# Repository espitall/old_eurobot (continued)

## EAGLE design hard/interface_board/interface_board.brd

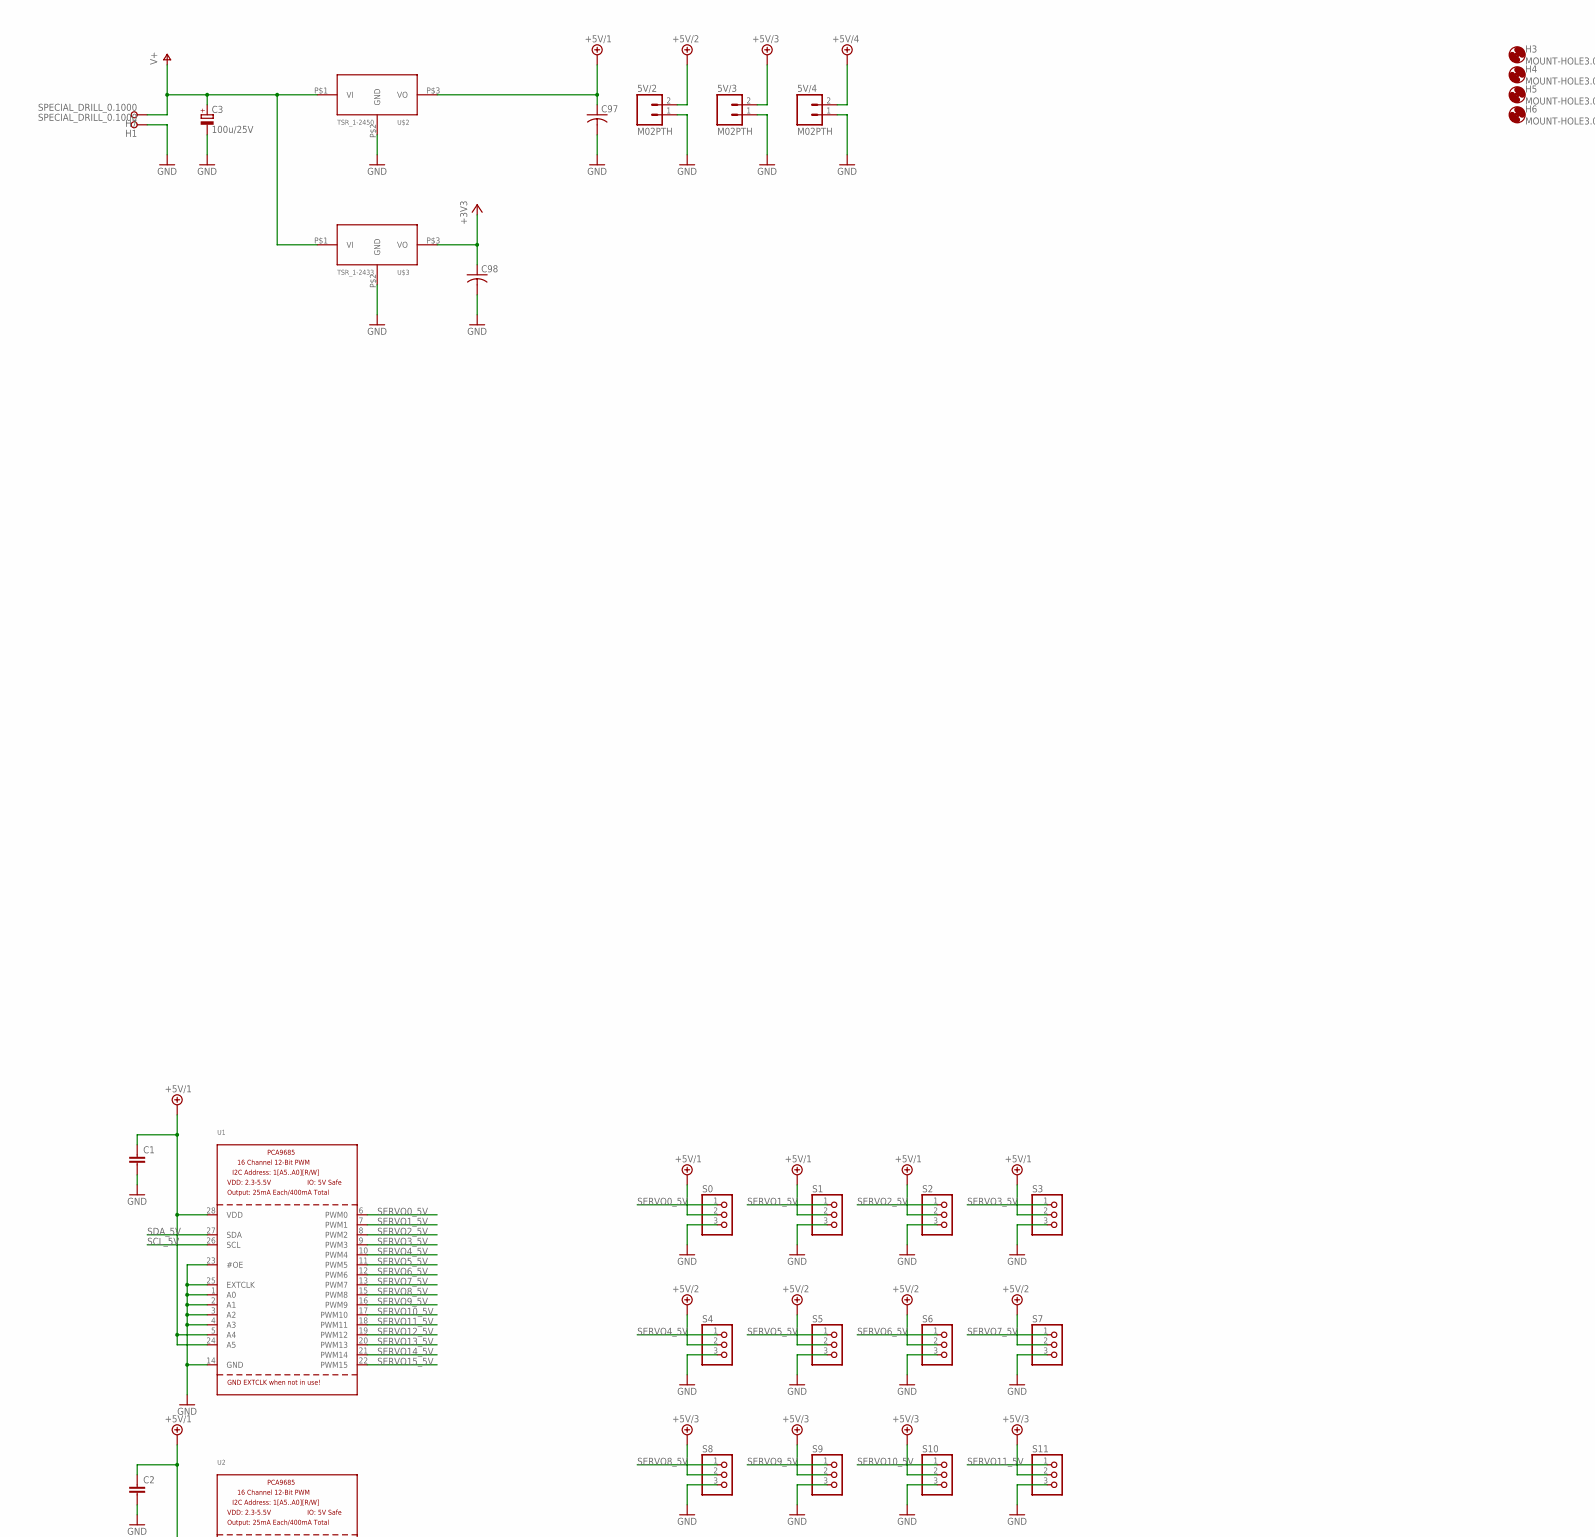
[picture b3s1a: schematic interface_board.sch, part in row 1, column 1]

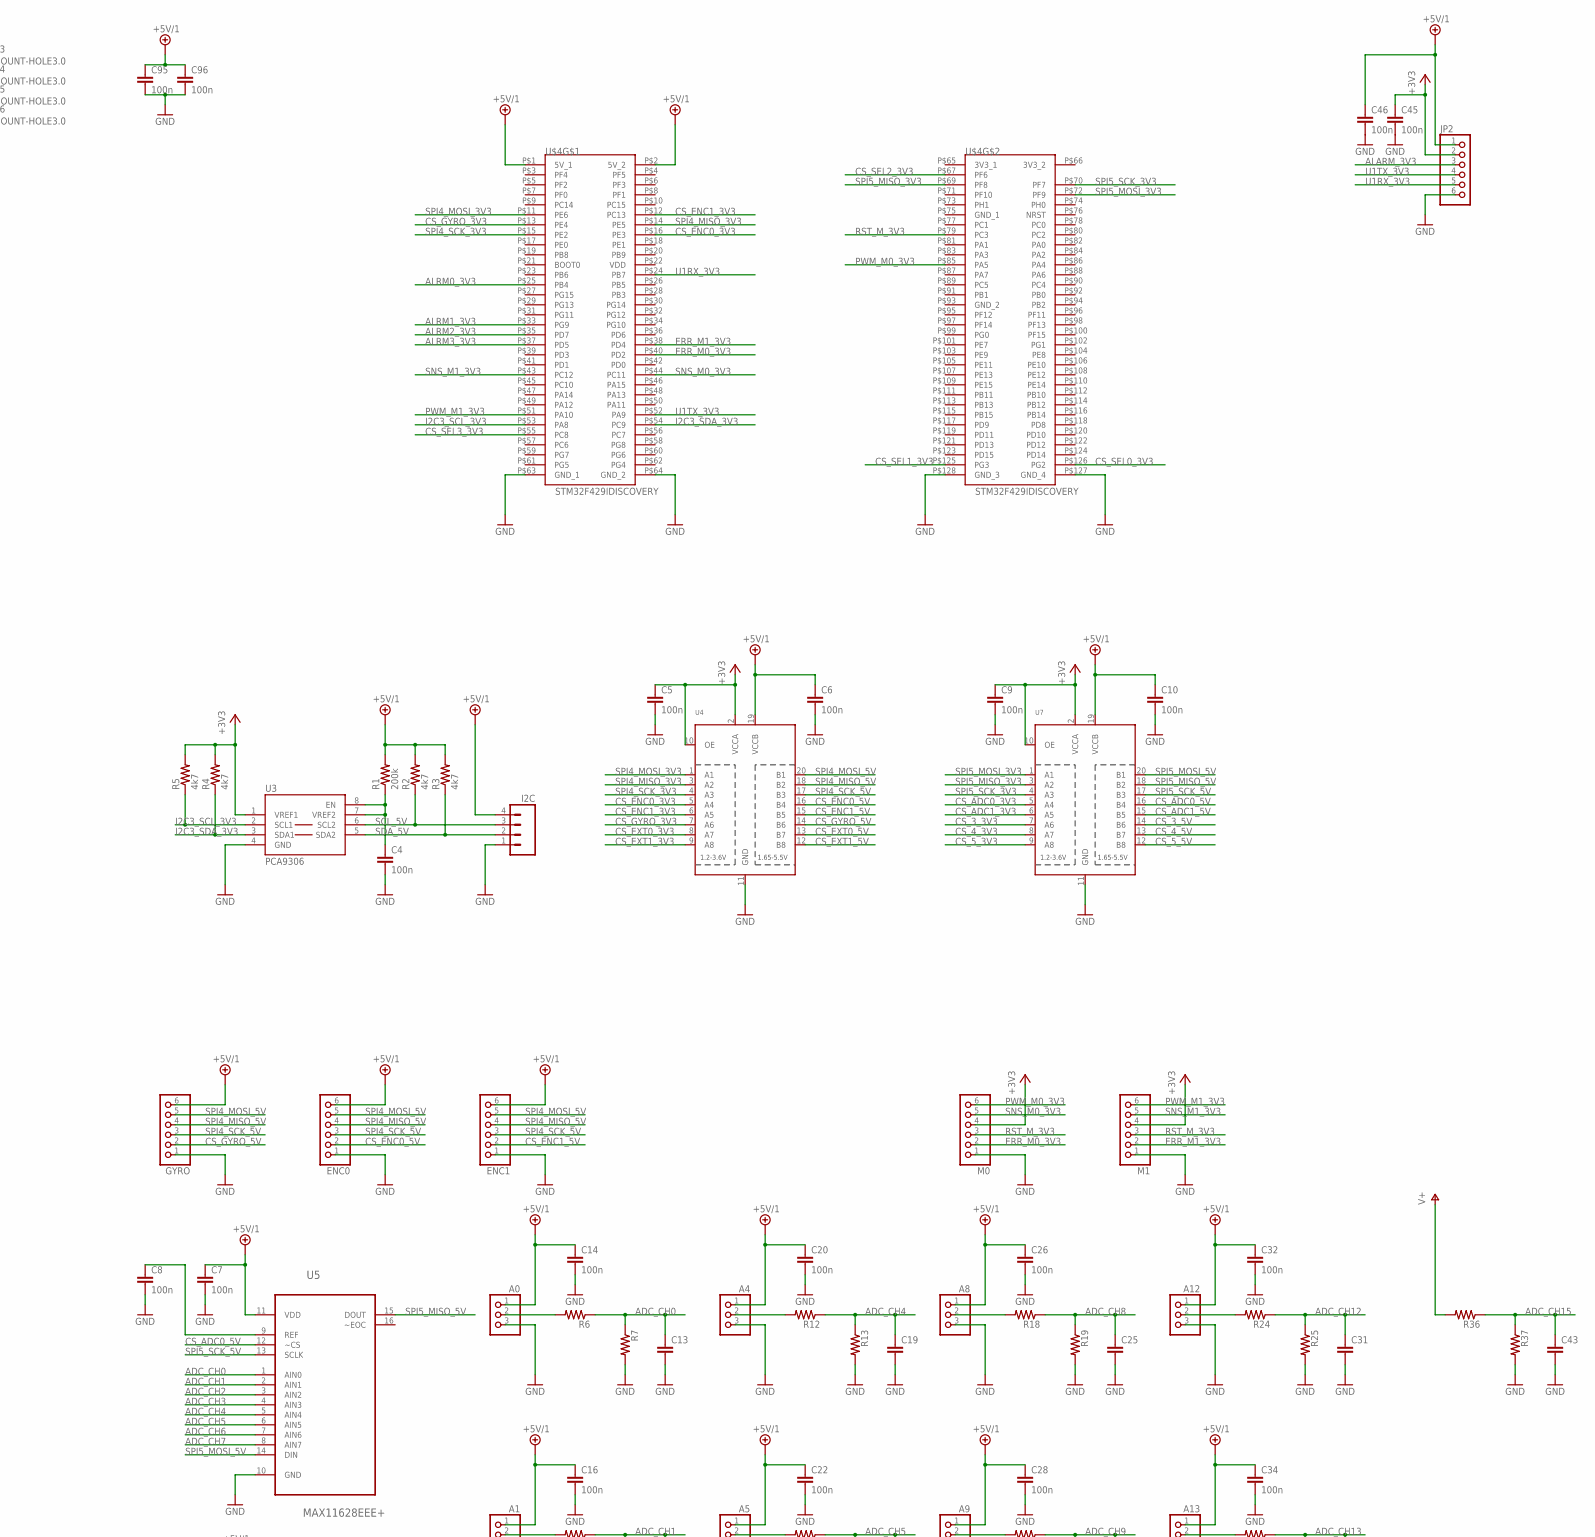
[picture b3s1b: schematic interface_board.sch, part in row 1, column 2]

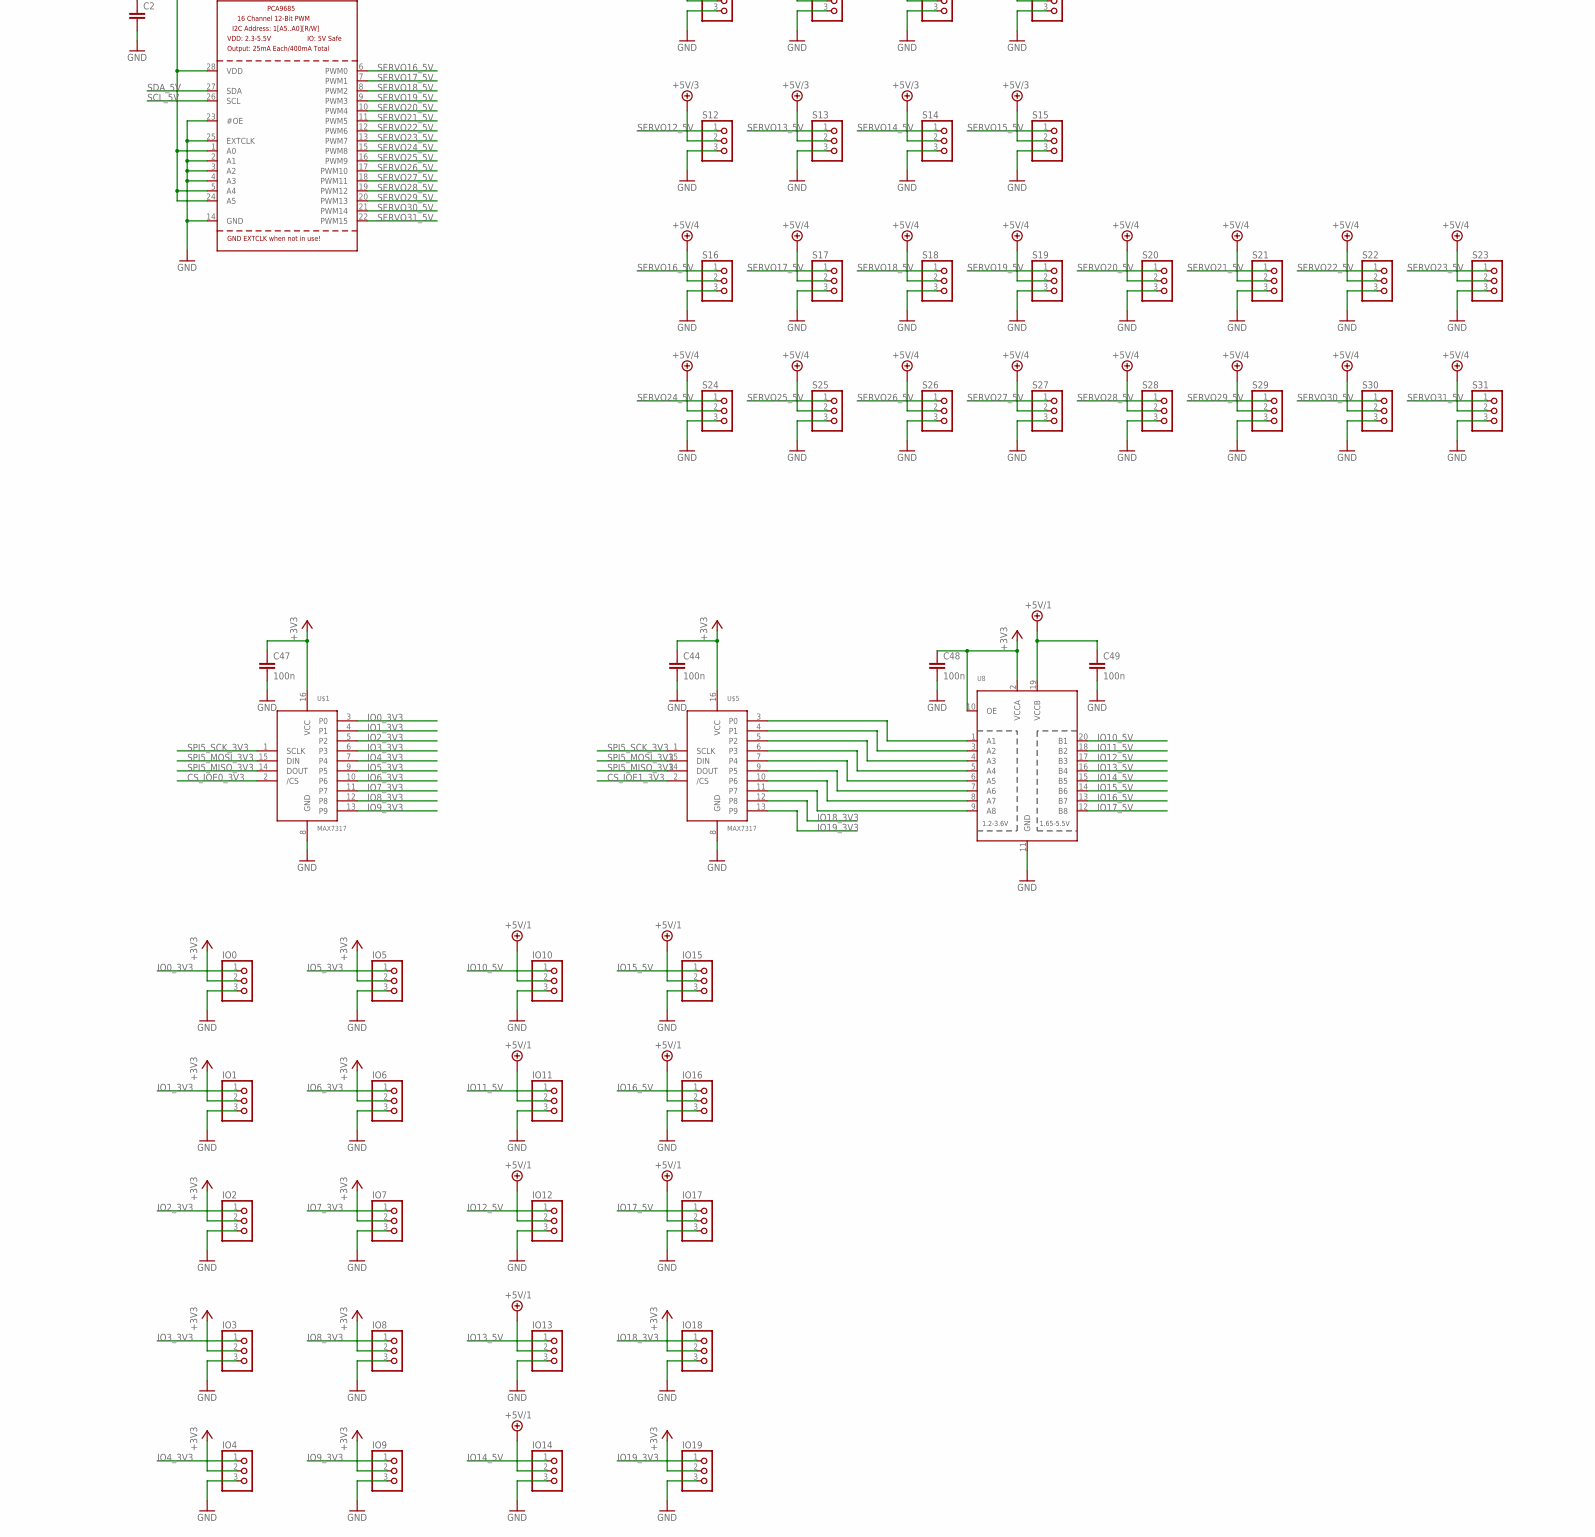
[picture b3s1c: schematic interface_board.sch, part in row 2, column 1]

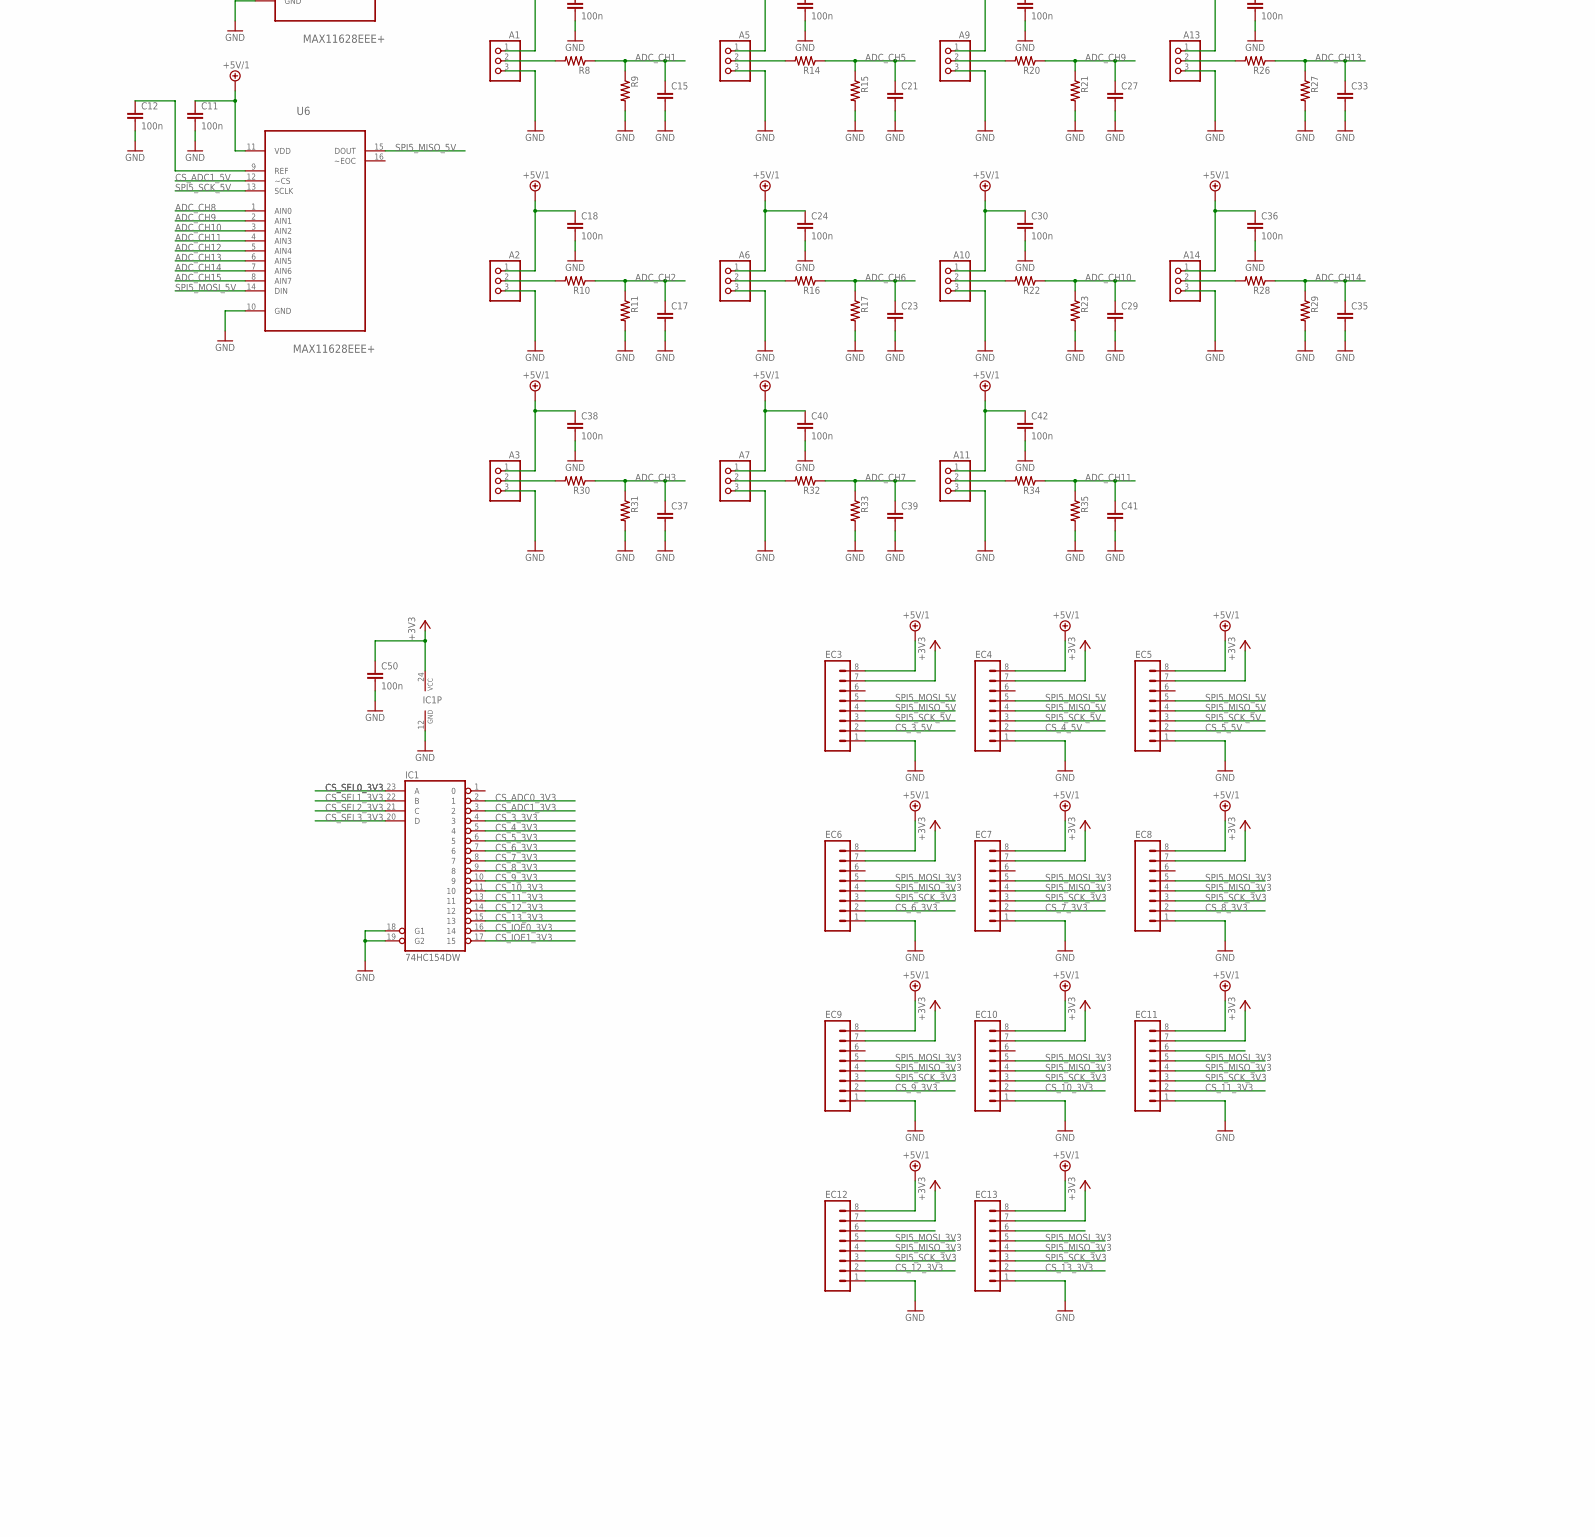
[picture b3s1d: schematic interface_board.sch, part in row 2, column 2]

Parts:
5V/2, 5V/3, 5V/4: M02PTH; 1X02
A0, A1, A2, A3, A4, A5, A6, A7, A8, A9, A10, A11, A12, A13, A14: PINHD-1X3; 1X03
C1, C2, C13, C15, C17, C19, C21, C23, C25, C27, C29, C31, C33, C35, C37, C39, C41, C43: C-EUC0603K; C0603K
C3: 100u/25V; PANASONIC_E
C4, C5, C6, C7, C8, C9, C10, C11, C12, C14, C16, C18, C20, C22, C24, C26, C28, C30, C32, C34, C36, C38, C40, C42, C44, C45, C46, C47, C48, C49, C50, C95, C96: 100n; C0603K
C97, C98: C-USC0805; C0805
EC3, EC4, EC5, EC6, EC7, EC8, EC9, EC10, EC11, EC12, EC13: M081X08; 1X08
ENC0, ENC1: PINHD-1X6; 1X06
GYRO: PINHD-1X6; 1X06
H1, H7: SPECIAL_DRILL_0.1000; PAD_0.1000
H3, H4, H5, H6: MOUNT-HOLE3.0; 3,0
I2C: M04PTH; 1X04
IC1: 74HC154DW; SO24W
IO0, IO1, IO2, IO3, IO4, IO5, IO6, IO7, IO8, IO9, IO10, IO11, IO12, IO13, IO14, IO15, IO16, IO17, IO18, IO19: PINHD-1X3; 1X03
JP2: PINHD-1X6B; 1X06-BIG
M0, M1: PINHD-1X6; 1X06
R1: 200k; R0603
R2, R3, R4, R5: 4k7; R0603
R6, R7, R8, R9, R10, R11, R12, R13, R14, R15, R16, R17, R18, R19, R20, R21, R22, R23, R24, R25, R26, R27, R28, R29, R30, R31, R32, R33, R34, R35, R36, R37: R-US_R0603; R0603
S0, S1, S2, S3, S4, S5, S6, S7, S8, S9, S10, S11, S12, S13, S14, S15, S16, S17, S18, S19, S20, S21, S22, S23, S24, S25, S26, S27, S28, S29, S30, S31: PINHD-1X3; 1X03
U1, U2: PCA9685; TSSOP28
U3: PCA9306; PSOP-8
U4, U7, U8: TXB0108PWR; TSSOP20
U5, U6: MAX11628EEE+; SOP63P602X175-16N
U$1, U$5: MAX7317; SOP63P600X175-16N
U$2: TSR_1-2450; TSR-1
U$3: TSR_1-2433; TSR-1
U$4: STM32F429IDISCOVERY

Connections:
+3V3: C5.1, C9.1, C44.1, C45.1, C47.1, C48.1, C50.1, C98.1, EC3.7, EC4.7, EC5.7, EC6.7, EC7.7, EC8.7, EC9.7, EC10.7, EC11.7, EC12.7, EC13.7, IC1.24 (VCC), IO0.2, IO1.2, IO2.2, IO3.2, IO4.2, IO5.2, IO6.2, IO7.2, IO8.2, IO9.2, IO18.2, IO19.2, JP2.2, M0.4, M1.4, R4.2, R5.2, U3.1 (VREF1), U4.2 (VCCA), U4.10 (OE), U7.2 (VCCA), U7.10 (OE), U8.2 (VCCA), U8.10 (OE), U$1.16 (VCC), U$3.P$3 (VO), U$5.16 (VCC)
+5V/1: A0.1, A1.1, A2.1, A3.1, A4.1, A5.1, A6.1, A7.1, A8.1, A9.1, A10.1, A11.1, A12.1, A13.1, A14.1, C1.1, C2.1, C6.1, C7.1, C10.1, C11.1, C14.1, C16.1, C18.1, C20.1, C22.1, C24.1, C26.1, C28.1, C30.1, C32.1, C34.1, C36.1, C38.1, C40.1, C42.1, C46.1, C49.1, C95.1, C96.1, C97.1, EC3.8, EC4.8, EC5.8, EC6.8, EC7.8, EC8.8, EC9.8, EC10.8, EC11.8, EC12.8, EC13.8, ENC0.6, ENC1.6, GYRO.6, I2C.4, IO10.2, IO11.2, IO12.2, IO13.2, IO14.2, IO15.2, IO16.2, IO17.2, JP2.1, R1.2, R2.2, R3.2, S0.2, S1.2, S2.2, S3.2, U1.5 (A4), U1.24 (A5), U1.28 (VDD), U2.1 (A0), U2.5 (A4), U2.24 (A5), U2.28 (VDD), U4.19 (VCCB), U5.11 (VDD), U6.11 (VDD), U7.19 (VCCB), U8.19 (VCCB), U$2.P$3 (VO), U$4.P$1 (5V_1), U$4.P$2 (5V_2)
+5V/2: 5V/2.2, S4.2, S5.2, S6.2, S7.2
+5V/3: 5V/3.2, S8.2, S9.2, S10.2, S11.2, S12.2, S13.2, S14.2, S15.2
+5V/4: 5V/4.2, S16.2, S17.2, S18.2, S19.2, S20.2, S21.2, S22.2, S23.2, S24.2, S25.2, S26.2, S27.2, S28.2, S29.2, S30.2, S31.2
ADC_CH0: C13.1, R6.1, R7.1, U5.1 (AIN0)
ADC_CH1: C15.1, R8.1, R9.1, U5.2 (AIN1)
ADC_CH2: C17.1, R10.1, R11.1, U5.3 (AIN2)
ADC_CH3: C37.1, R30.1, R31.1, U5.4 (AIN3)
ADC_CH4: C19.1, R12.1, R13.1, U5.5 (AIN4)
ADC_CH5: C21.1, R14.1, R15.1, U5.6 (AIN5)
ADC_CH6: C23.1, R16.1, R17.1, U5.7 (AIN6)
ADC_CH7: C39.1, R32.1, R33.1, U5.8 (AIN7)
ADC_CH8: C25.1, R18.1, R19.1, U6.1 (AIN0)
ADC_CH9: C27.1, R20.1, R21.1, U6.2 (AIN1)
ADC_CH10: C29.1, R22.1, R23.1, U6.3 (AIN2)
ADC_CH11: C41.1, R34.1, R35.1, U6.4 (AIN3)
ADC_CH12: C31.1, R24.1, R25.1, U6.5 (AIN4)
ADC_CH13: C33.1, R26.1, R27.1, U6.6 (AIN5)
ADC_CH14: C35.1, R28.1, R29.1, U6.7 (AIN6)
ADC_CH15: C43.1, R36.1, R37.1, U6.8 (AIN7)
ALARM_3V3: JP2.3
ALRM0_3V3: U$4.P$25 (PB4)
ALRM1_3V3: EC11.6, U$4.P$33 (PG9)
ALRM2_3V3: EC12.6, U$4.P$35 (PD7)
ALRM3_3V3: EC13.6, U$4.P$37 (PD5)
CS_3_3V3: IC1.4 (3), U7.7 (A6)
CS_3_5V: EC3.2, U7.14 (B6)
CS_4_3V3: IC1.5 (4), U7.8 (A7)
CS_4_5V: EC4.2, U7.13 (B7)
CS_5_3V3: IC1.6 (5), U7.9 (A8)
CS_5_5V: EC5.2, U7.12 (B8)
CS_6_3V3: EC6.2, IC1.7 (6)
CS_7_3V3: EC7.2, IC1.8 (7)
CS_8_3V3: EC8.2, IC1.9 (8)
CS_9_3V3: EC9.2, IC1.10 (9)
CS_10_3V3: EC10.2, IC1.11 (10)
CS_11_3V3: EC11.2, IC1.13 (11)
CS_12_3V3: EC12.2, IC1.14 (12)
CS_13_3V3: EC13.2, IC1.15 (13)
CS_ADC0_3V3: IC1.2 (1), U7.5 (A4)
CS_ADC0_5V: U5.12 (~CS), U7.16 (B4)
CS_ADC1_3V3: IC1.3 (2), U7.6 (A5)
CS_ADC1_5V: U6.12 (~CS), U7.15 (B5)
CS_ENC0_3V3: U4.5 (A4), U$4.P$16 (PE3)
CS_ENC0_5V: ENC0.2, U4.16 (B4)
CS_ENC1_3V3: U4.6 (A5), U$4.P$12 (PC13)
CS_ENC1_5V: ENC1.2, U4.15 (B5)
CS_EXT0_3V3: U4.8 (A7)
CS_EXT0_5V: U4.13 (B7)
CS_EXT1_3V3: U4.9 (A8)
CS_EXT1_5V: U4.12 (B8)
CS_GYRO_3V3: U4.7 (A6), U$4.P$13 (PE4)
CS_GYRO_5V: GYRO.2, U4.14 (B6)
CS_IOE0_3V3: IC1.16 (14), U$1.2 (/CS)
CS_IOE1_3V3: IC1.17 (15), U$5.2 (/CS)
CS_SEL0_3V3: IC1.23 (A), U$4.P$126 (PG2)
CS_SEL1_3V3: IC1.22 (B), U$4.P$125 (PG3)
CS_SEL2_3V3: IC1.21 (C), U$4.P$67 (PF6)
CS_SEL3_3V3: IC1.20 (D), U$4.P$55 (PC8)
ERR_M0_3V3: M0.2, U$4.P$40 (PD2)
ERR_M1_3V3: M1.2, U$4.P$38 (PD4)
GND: 5V/2.1, 5V/3.1, 5V/4.1, A0.3, A1.3, A2.3, A3.3, A4.3, A5.3, A6.3, A7.3, A8.3, A9.3, A10.3, A11.3, A12.3, A13.3, A14.3, C1.2, C2.2, C3.-, C4.2, C5.2, C6.2, C7.2, C8.2, C9.2, C10.2, C11.2, C12.2, C13.2, C14.2, C15.2, C16.2, C17.2, C18.2, C19.2, C20.2, C21.2, C22.2, C23.2, C24.2, C25.2, C26.2, C27.2, C28.2, C29.2, C30.2, C31.2, C32.2, C33.2, C34.2, C35.2, C36.2, C37.2, C38.2, C39.2, C40.2, C41.2, C42.2, C43.2, C44.2, C45.2, C46.2, C47.2, C48.2, C49.2, C50.2, C95.2, C96.2, C97.2, C98.2, EC3.1, EC4.1, EC5.1, EC6.1, EC7.1, EC8.1, EC9.1, EC10.1, EC11.1, EC12.1, EC13.1, ENC0.1, ENC1.1, GYRO.1, H1.1, I2C.1, IC1.12 (GND), IC1.18 (G1), IC1.19 (G2), IO0.3, IO1.3, IO2.3, IO3.3, IO4.3, IO5.3, IO6.3, IO7.3, IO8.3, IO9.3, IO10.3, IO11.3, IO12.3, IO13.3, IO14.3, IO15.3, IO16.3, IO17.3, IO18.3, IO19.3, JP2.6, M0.1, M1.1, R7.2, R9.2, R11.2, R13.2, R15.2, R17.2, R19.2, R21.2, R23.2, R25.2, R27.2, R29.2, R31.2, R33.2, R35.2, R37.2, S0.3, S1.3, S2.3, S3.3, S4.3, S5.3, S6.3, S7.3, S8.3, S9.3, S10.3, S11.3, S12.3, S13.3, S14.3, S15.3, S16.3, S17.3, S18.3, S19.3, S20.3, S21.3, S22.3, S23.3, S24.3, S25.3, S26.3, S27.3, S28.3, S29.3, S30.3, S31.3, U1.1 (A0), U1.2 (A1), U1.3 (A2), U1.4 (A3), U1.14 (GND), U1.23 (#OE), U1.25 (EXTCLK), U2.2 (A1), U2.3 (A2), U2.4 (A3), U2.14 (GND), U2.23 (#OE), U2.25 (EXTCLK), U3.4 (GND), U4.11 (GND), U5.10 (GND), U6.10 (GND), U7.11 (GND), U8.11 (GND), U$1.8 (GND), U$2.P$2 (GND), U$3.P$2 (GND), U$4.P$63 (GND_1), U$4.P$64 (GND_2), U$4.P$127 (GND_4), U$4.P$128 (GND_3), U$5.8 (GND)
I2C3_SCL_3V3: R5.1, U3.2 (SCL1), U$4.P$53 (PA8)
I2C3_SDA_3V3: R4.1, U3.3 (SDA1), U$4.P$54 (PC9)
IO0_3V3: IO0.1, U$1.3 (P0)
IO1_3V3: IO1.1, U$1.4 (P1)
IO2_3V3: IO2.1, U$1.5 (P2)
IO3_3V3: IO3.1, U$1.6 (P3)
IO4_3V3: IO4.1, U$1.7 (P4)
IO5_3V3: IO5.1, U$1.9 (P5)
IO6_3V3: IO6.1, U$1.10 (P6)
IO7_3V3: IO7.1, U$1.11 (P7)
IO8_3V3: IO8.1, U$1.12 (P8)
IO9_3V3: IO9.1, U$1.13 (P9)
IO10_5V: IO10.1, U8.20 (B1)
IO11_5V: IO11.1, U8.18 (B2)
IO12_5V: IO12.1, U8.17 (B3)
IO13_5V: IO13.1, U8.16 (B4)
IO14_5V: IO14.1, U8.15 (B5)
IO15_5V: IO15.1, U8.14 (B6)
IO16_5V: IO16.1, U8.13 (B7)
IO17_5V: IO17.1, U8.12 (B8)
IO18_3V3: IO18.1, U$5.12 (P8)
IO19_3V3: IO19.1, U$5.13 (P9)
unnamed: C8.1, U5.9 (REF)
unnamed: C12.1, U6.9 (REF)
unnamed: C4.1, R1.1, U3.7 (VREF2), U3.8 (EN)
unnamed: A1.2, R8.2
unnamed: U8.1 (A1), U$5.3 (P0)
unnamed: A2.2, R10.2
unnamed: A0.2, R6.2
unnamed: A4.2, R12.2
unnamed: A5.2, R14.2
unnamed: A6.2, R16.2
unnamed: A8.2, R18.2
unnamed: A9.2, R20.2
unnamed: A10.2, R22.2
unnamed: A12.2, R24.2
unnamed: A13.2, R26.2
unnamed: A14.2, R28.2
unnamed: A3.2, R30.2
unnamed: A7.2, R32.2
unnamed: A11.2, R34.2
unnamed: U8.3 (A2), U$5.4 (P1)
unnamed: U8.4 (A3), U$5.5 (P2)
unnamed: U8.5 (A4), U$5.6 (P3)
unnamed: U8.6 (A5), U$5.7 (P4)
unnamed: U8.7 (A6), U$5.9 (P5)
unnamed: U8.8 (A7), U$5.10 (P6)
unnamed: U8.9 (A8), U$5.11 (P7)
PWM_M0_3V3: M0.6, U$4.P$85 (PA5)
PWM_M1_3V3: M1.6, U$4.P$51 (PA10)
RST_M_3V3: M0.3, M1.3, U$4.P$79 (PC3)
SCL_5V: I2C.3, R2.1, U1.26 (SCL), U2.26 (SCL), U3.6 (SCL2)
SDA_5V: I2C.2, R3.1, U1.27 (SDA), U2.27 (SDA), U3.5 (SDA2)
SERVO0_5V: S0.1, U1.6 (PWM0)
SERVO1_5V: S1.1, U1.7 (PWM1)
SERVO2_5V: S2.1, U1.8 (PWM2)
SERVO3_5V: S3.1, U1.9 (PWM3)
SERVO4_5V: S4.1, U1.10 (PWM4)
SERVO5_5V: S5.1, U1.11 (PWM5)
SERVO6_5V: S6.1, U1.12 (PWM6)
SERVO7_5V: S7.1, U1.13 (PWM7)
SERVO8_5V: S8.1, U1.15 (PWM8)
SERVO9_5V: S9.1, U1.16 (PWM9)
SERVO10_5V: S10.1, U1.17 (PWM10)
SERVO11_5V: S11.1, U1.18 (PWM11)
SERVO12_5V: S12.1, U1.19 (PWM12)
SERVO13_5V: S13.1, U1.20 (PWM13)
SERVO14_5V: S14.1, U1.21 (PWM14)
SERVO15_5V: S15.1, U1.22 (PWM15)
SERVO16_5V: S16.1, U2.6 (PWM0)
SERVO17_5V: S17.1, U2.7 (PWM1)
SERVO18_5V: S18.1, U2.8 (PWM2)
SERVO19_5V: S19.1, U2.9 (PWM3)
SERVO20_5V: S20.1, U2.10 (PWM4)
SERVO21_5V: S21.1, U2.11 (PWM5)
SERVO22_5V: S22.1, U2.12 (PWM6)
SERVO23_5V: S23.1, U2.13 (PWM7)
SERVO24_5V: S24.1, U2.15 (PWM8)
SERVO25_5V: S25.1, U2.16 (PWM9)
SERVO26_5V: S26.1, U2.17 (PWM10)
SERVO27_5V: S27.1, U2.18 (PWM11)
SERVO28_5V: S28.1, U2.19 (PWM12)
SERVO29_5V: S29.1, U2.20 (PWM13)
SERVO30_5V: S30.1, U2.21 (PWM14)
SERVO31_5V: S31.1, U2.22 (PWM15)
SNS_M0_3V3: M0.5, U$4.P$44 (PC11)
SNS_M1_3V3: M1.5, U$4.P$43 (PC12)
SPI4_MISO_3V3: U4.3 (A2), U$4.P$14 (PE5)
SPI4_MISO_5V: ENC0.4, ENC1.4, GYRO.4, U4.18 (B2)
SPI4_MOSI_3V3: U4.1 (A1), U$4.P$11 (PE6)
SPI4_MOSI_5V: ENC0.5, ENC1.5, GYRO.5, U4.20 (B1)
SPI4_SCK_3V3: U4.4 (A3), U$4.P$15 (PE2)
SPI4_SCK_5V: ENC0.3, ENC1.3, GYRO.3, U4.17 (B3)
SPI5_MISO_3V3: EC6.4, EC7.4, EC8.4, EC9.4, EC10.4, EC11.4, EC12.4, EC13.4, U7.3 (A2), U$1.14 (DOUT), U$4.P$69 (PF8), U$5.14 (DOUT)
SPI5_MISO_5V: EC3.4, EC4.4, EC5.4, U5.15 (DOUT), U6.15 (DOUT), U7.18 (B2)
SPI5_MOSI_3V3: EC6.5, EC7.5, EC8.5, EC9.5, EC10.5, EC11.5, EC12.5, EC13.5, U7.1 (A1), U$1.15 (DIN), U$4.P$72 (PF9), U$5.15 (DIN)
SPI5_MOSI_5V: EC3.5, EC4.5, EC5.5, U5.14 (DIN), U6.14 (DIN), U7.20 (B1)
SPI5_SCK_3V3: EC6.3, EC7.3, EC8.3, EC9.3, EC10.3, EC11.3, EC12.3, EC13.3, U7.4 (A3), U$1.1 (SCLK), U$4.P$70 (PF7), U$5.1 (SCLK)
SPI5_SCK_5V: EC3.3, EC4.3, EC5.3, U5.13 (SCLK), U6.13 (SCLK), U7.17 (B3)
U1RX_3V3: JP2.5, U$4.P$24 (PB7)
U1TX_3V3: JP2.4, U$4.P$52 (PA9)
V+: C3.+, H7.1, R36.2, U$2.P$1 (VI), U$3.P$1 (VI)

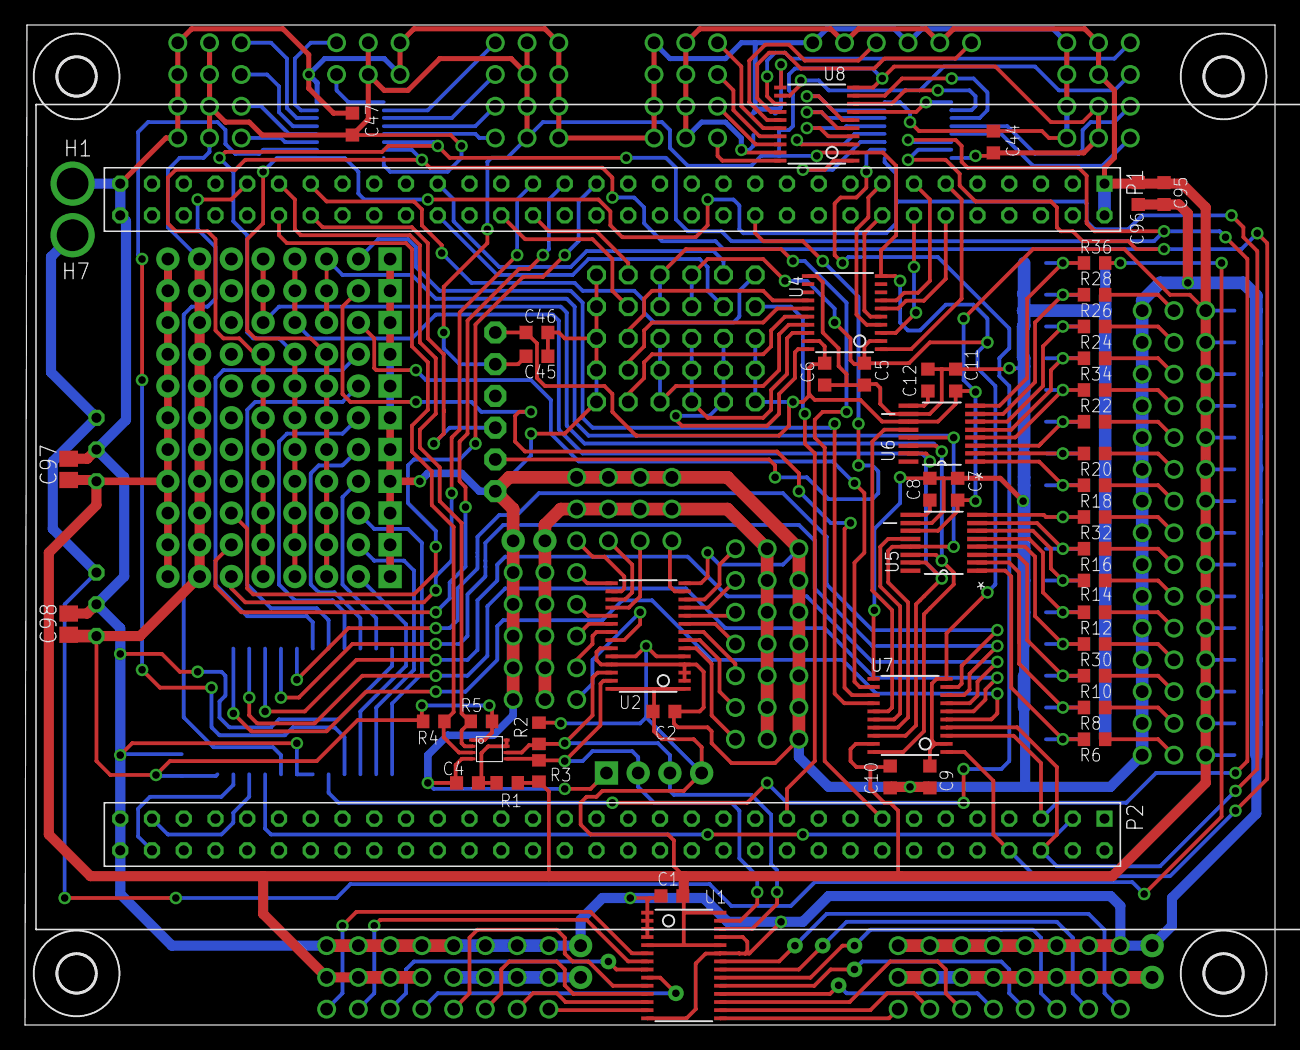
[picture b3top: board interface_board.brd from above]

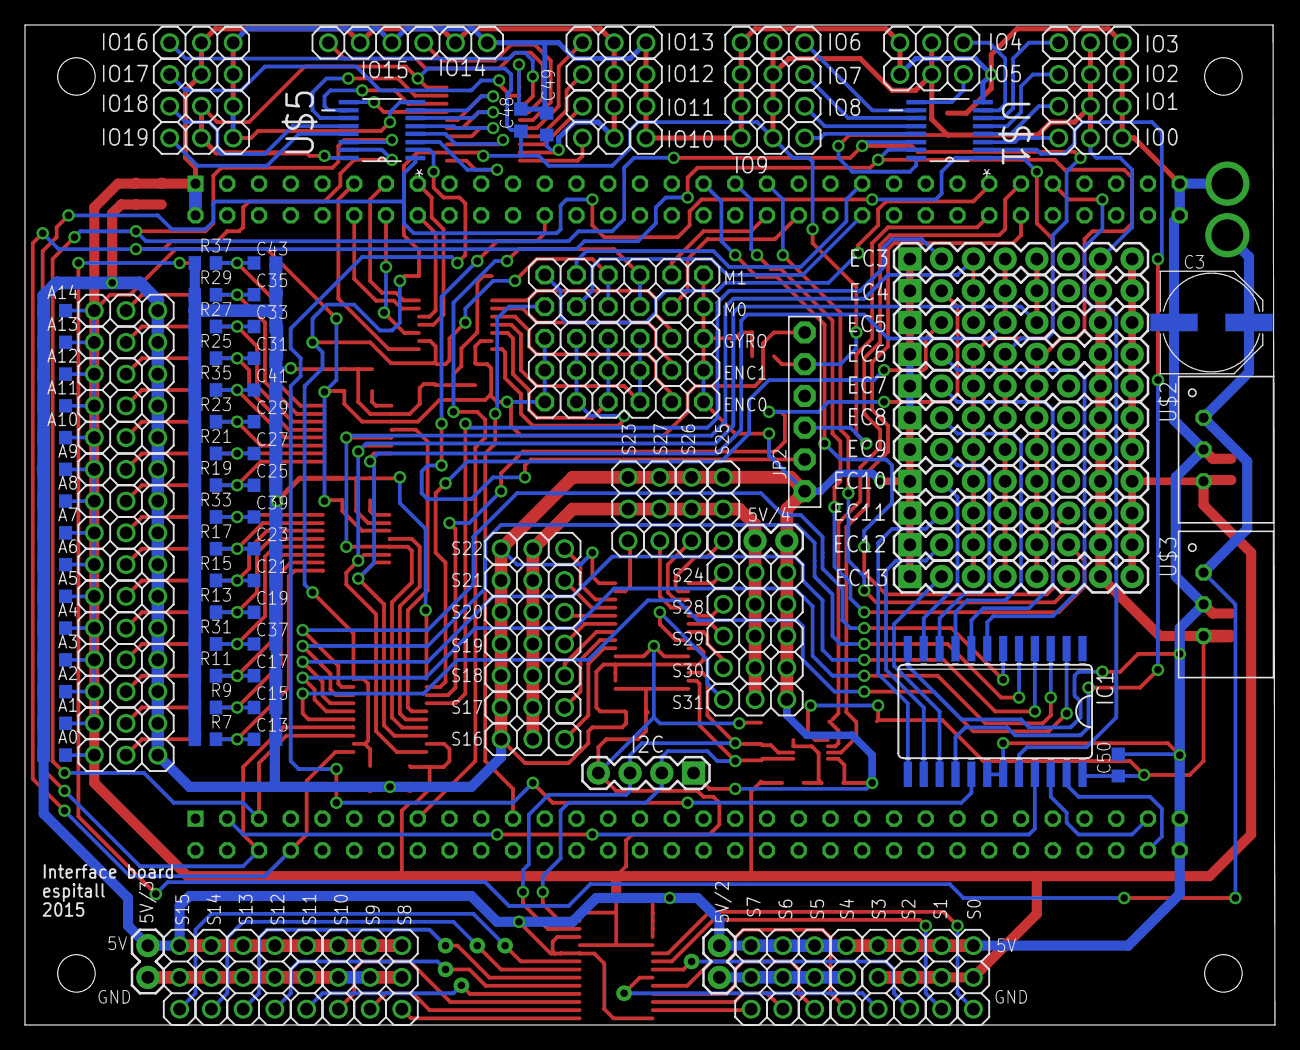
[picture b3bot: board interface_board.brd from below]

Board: 2 copper layers, 100.0 x 80.0 mm, 199 parts (144 on the bottom side), 159 nets.

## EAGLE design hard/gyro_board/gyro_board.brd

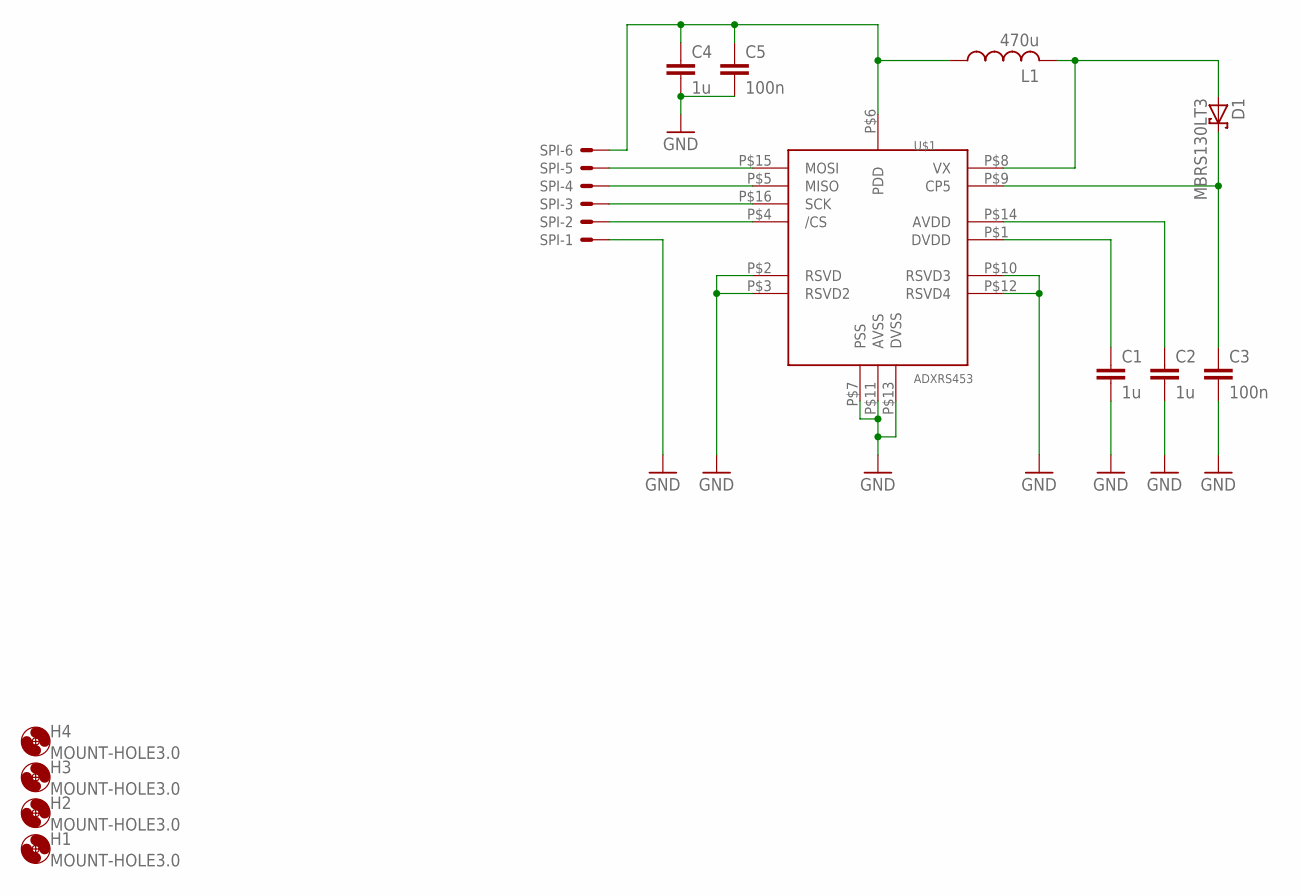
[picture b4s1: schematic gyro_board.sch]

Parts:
C1, C2, C4: 1u; C0603
C3, C5: 100n; C0603
D1: MBRS130LT3; SMB
H1, H2, H3, H4: MOUNT-HOLE3.0; 3,0
L1: 470u; L1812
SPI: 22-23-2061
U$1: ADXRS453; SOIC_CAV

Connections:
GND: C1.2, C2.2, C3.2, C4.2, C5.2, SPI.1, U$1.P$2 (RSVD), U$1.P$3 (RSVD2), U$1.P$7 (PSS), U$1.P$10 (RSVD3), U$1.P$11 (AVSS), U$1.P$12 (RSVD4), U$1.P$13 (DVSS)
unnamed: SPI.5, U$1.P$15 (MOSI)
unnamed: C4.1, C5.1, L1.1, SPI.6, U$1.P$6 (PDD)
unnamed: D1.A, L1.2, U$1.P$8 (VX)
unnamed: C1.1, U$1.P$1 (DVDD)
unnamed: C2.1, U$1.P$14 (AVDD)
unnamed: C3.1, D1.C, U$1.P$9 (CP5)
unnamed: SPI.2, U$1.P$4 (/CS)
unnamed: SPI.3, U$1.P$16 (SCK)
unnamed: SPI.4, U$1.P$5 (MISO)

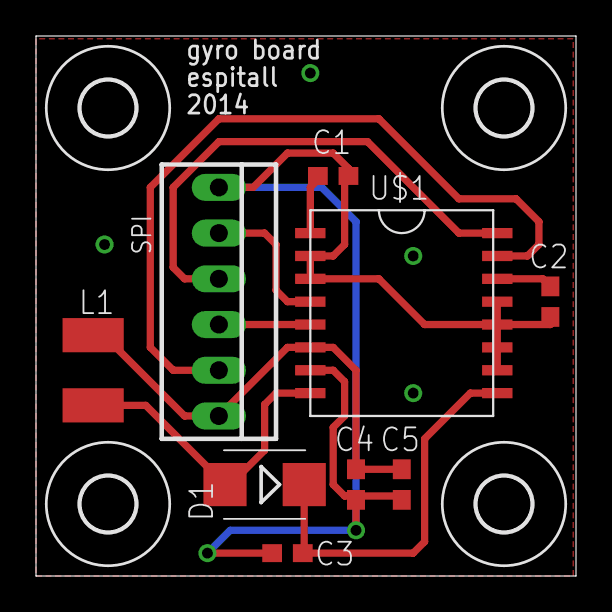
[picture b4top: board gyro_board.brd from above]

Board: 2 copper layers, 30.0 x 30.0 mm, 13 parts (0 on the bottom side), 10 nets.

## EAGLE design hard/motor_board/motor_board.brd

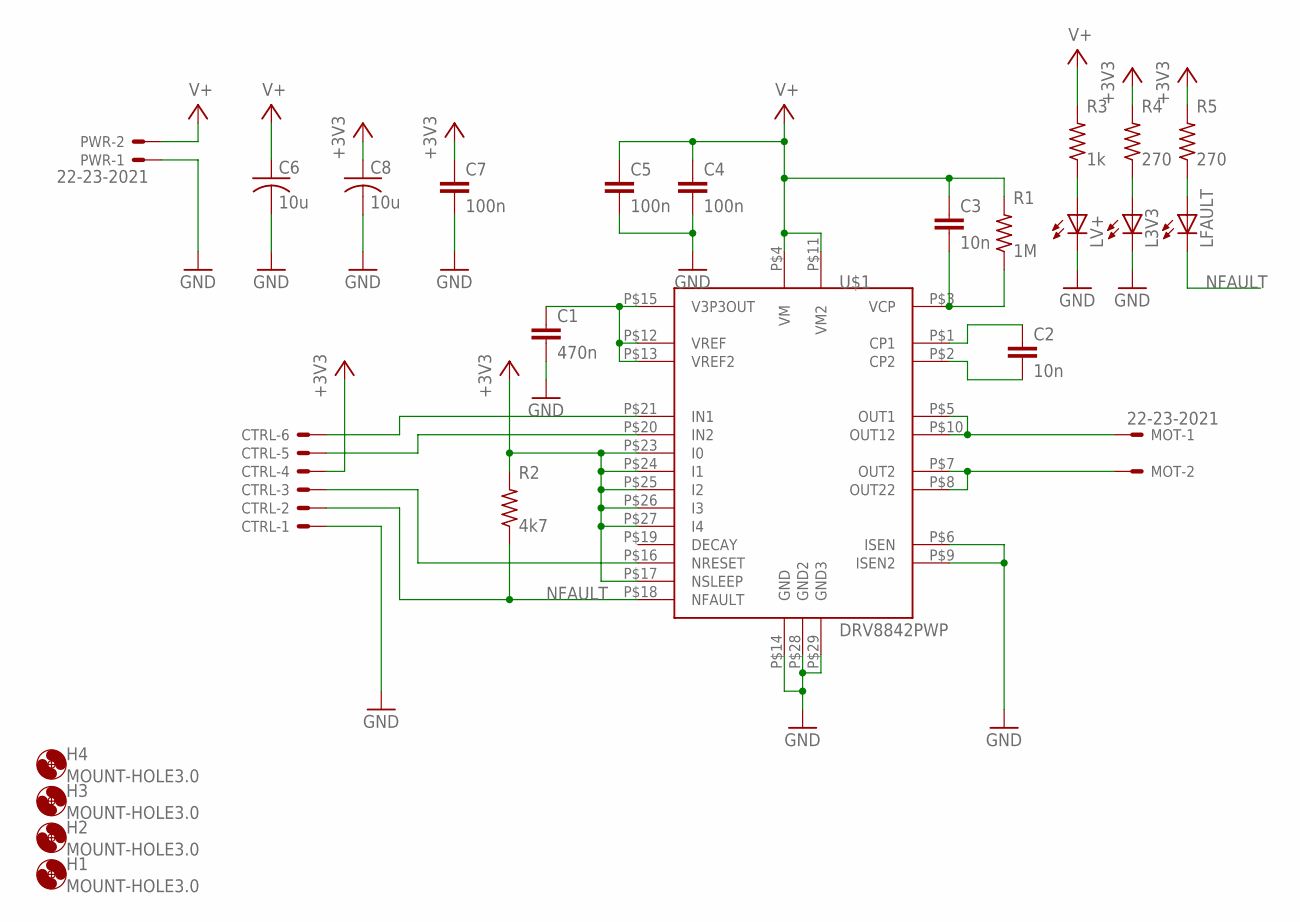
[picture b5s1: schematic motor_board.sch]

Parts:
C1: 470n; C0603K
C2, C3: 10n; C0603K
C4, C5, C7: 100n; C0603K
C6, C8: 10u; C0805K
CTRL: 22-23-2061
H1, H2, H3, H4: MOUNT-HOLE3.0; 3,0
L3V3: LEDCHIPLED_0603; CHIPLED_0603
LFAULT: LEDCHIPLED_0603; CHIPLED_0603
LV+: LEDCHIPLED_0603; CHIPLED_0603
MOT: 22-23-2021
PWR: 22-23-2021
R1: 1M; R0603
R2: 4k7; R0603
R3: 1k; R0603
R4, R5: 270; R0603
U$1: DRV8842PWP; R-PDS0-G28

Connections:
+3V3: C7.1, C8.1, CTRL.4, R2.2, R4.2, R5.2, U$1.P$17 (NSLEEP), U$1.P$23 (I0), U$1.P$24 (I1), U$1.P$25 (I2), U$1.P$26 (I3), U$1.P$27 (I4)
CP1: C2.1, U$1.P$1 (CP1)
CP2: C2.2, U$1.P$2 (CP2)
GND: C1.2, C4.2, C5.2, C6.2, C7.2, C8.2, CTRL.1, L3V3.C, LV+.C, PWR.1, U$1.P$6 (ISEN), U$1.P$9 (ISEN2), U$1.P$14 (GND), U$1.P$28 (GND2), U$1.P$29 (GND3)
IN1: CTRL.6, U$1.P$21 (IN1)
IN2: CTRL.5, U$1.P$20 (IN2)
unnamed: L3V3.A, R4.1
unnamed: LV+.A, R3.1
unnamed: LFAULT.A, R5.1
unnamed: C1.1, U$1.P$12 (VREF), U$1.P$13 (VREF2), U$1.P$15 (V3P3OUT)
NFAULT: CTRL.2, LFAULT.C, R2.1, U$1.P$18 (NFAULT)
NRESET: CTRL.3, U$1.P$16 (NRESET)
OUT1: MOT.1, U$1.P$5 (OUT1), U$1.P$10 (OUT12)
OUT2: MOT.2, U$1.P$7 (OUT2), U$1.P$8 (OUT22)
V+: C3.1, C4.1, C5.1, C6.1, PWR.2, R1.2, R3.2, U$1.P$4 (VM), U$1.P$11 (VM2)
VCP: C3.2, R1.1, U$1.P$3 (VCP)
